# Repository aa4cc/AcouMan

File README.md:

# AcouMan - a platform for acoustic manipulation
[index](README.md)

# _!! IMPORTANT -- repository relocated !!_
Content in this repo is no longer updated.
Go to (https://gitlab.fel.cvut.cz/aa4cc/acouman/acouman-main) to get the latest version.
# _!! !!_

AcouMan is a platform for acoustic manipulation, that is for manipulating objects via shaping the surrounding acoustic pressure field. You can see the platform in the figure below and a detailed description will be (hopefully) published soon. If you want to see the platform in action, check our [video](https://youtu.be/BdDq_jRSNYA) showing some experiments with the platform.

This repository contains all files needed to reproduce the platform.

* [_MATLAB Optimization/_](MATLAB&#32;optimization/readme.md) folder contains Matlab scripts implementing a solver of the optimization problem where one looks for such phase shifts of the signals driving the transducer array that a given pressure point in space is generated
* [_FPGA generator/_](FPGA_generator/readme.md) folder contains a Quartus project for the 64 channel generator
* [_calibration/_](calibration/readme.md) folder contains all scripts for calibrating the camera
* [_manufacturing/_](manufacturing/readme.md) folder contains all drawings for a laser cutter, 3D models and PCB designs for manufacturing the platform
* [_simulink/_](simulink/readme.md) folder contains Simulink schemes for controlling the platform in various modes
* [_visualization/_](visualization/readme.md) folder contains Matlab scripts for visualization of the generated pressure field by the transducer array driven by square waves with specified phase-shifts
* [_webinterface/_](webinterface/readme.md) folder contains Python scripts for the web interface running on the Raspberry Pi

## Building the platform

If you want to build the platform, please refer to the guides on [mechanical assembly](docs/assembly.md) and [software](docs/software.md).

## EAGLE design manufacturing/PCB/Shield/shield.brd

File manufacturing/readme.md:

# Manufacturing
[index](../README.md) \> [manufacturing](readme.md)

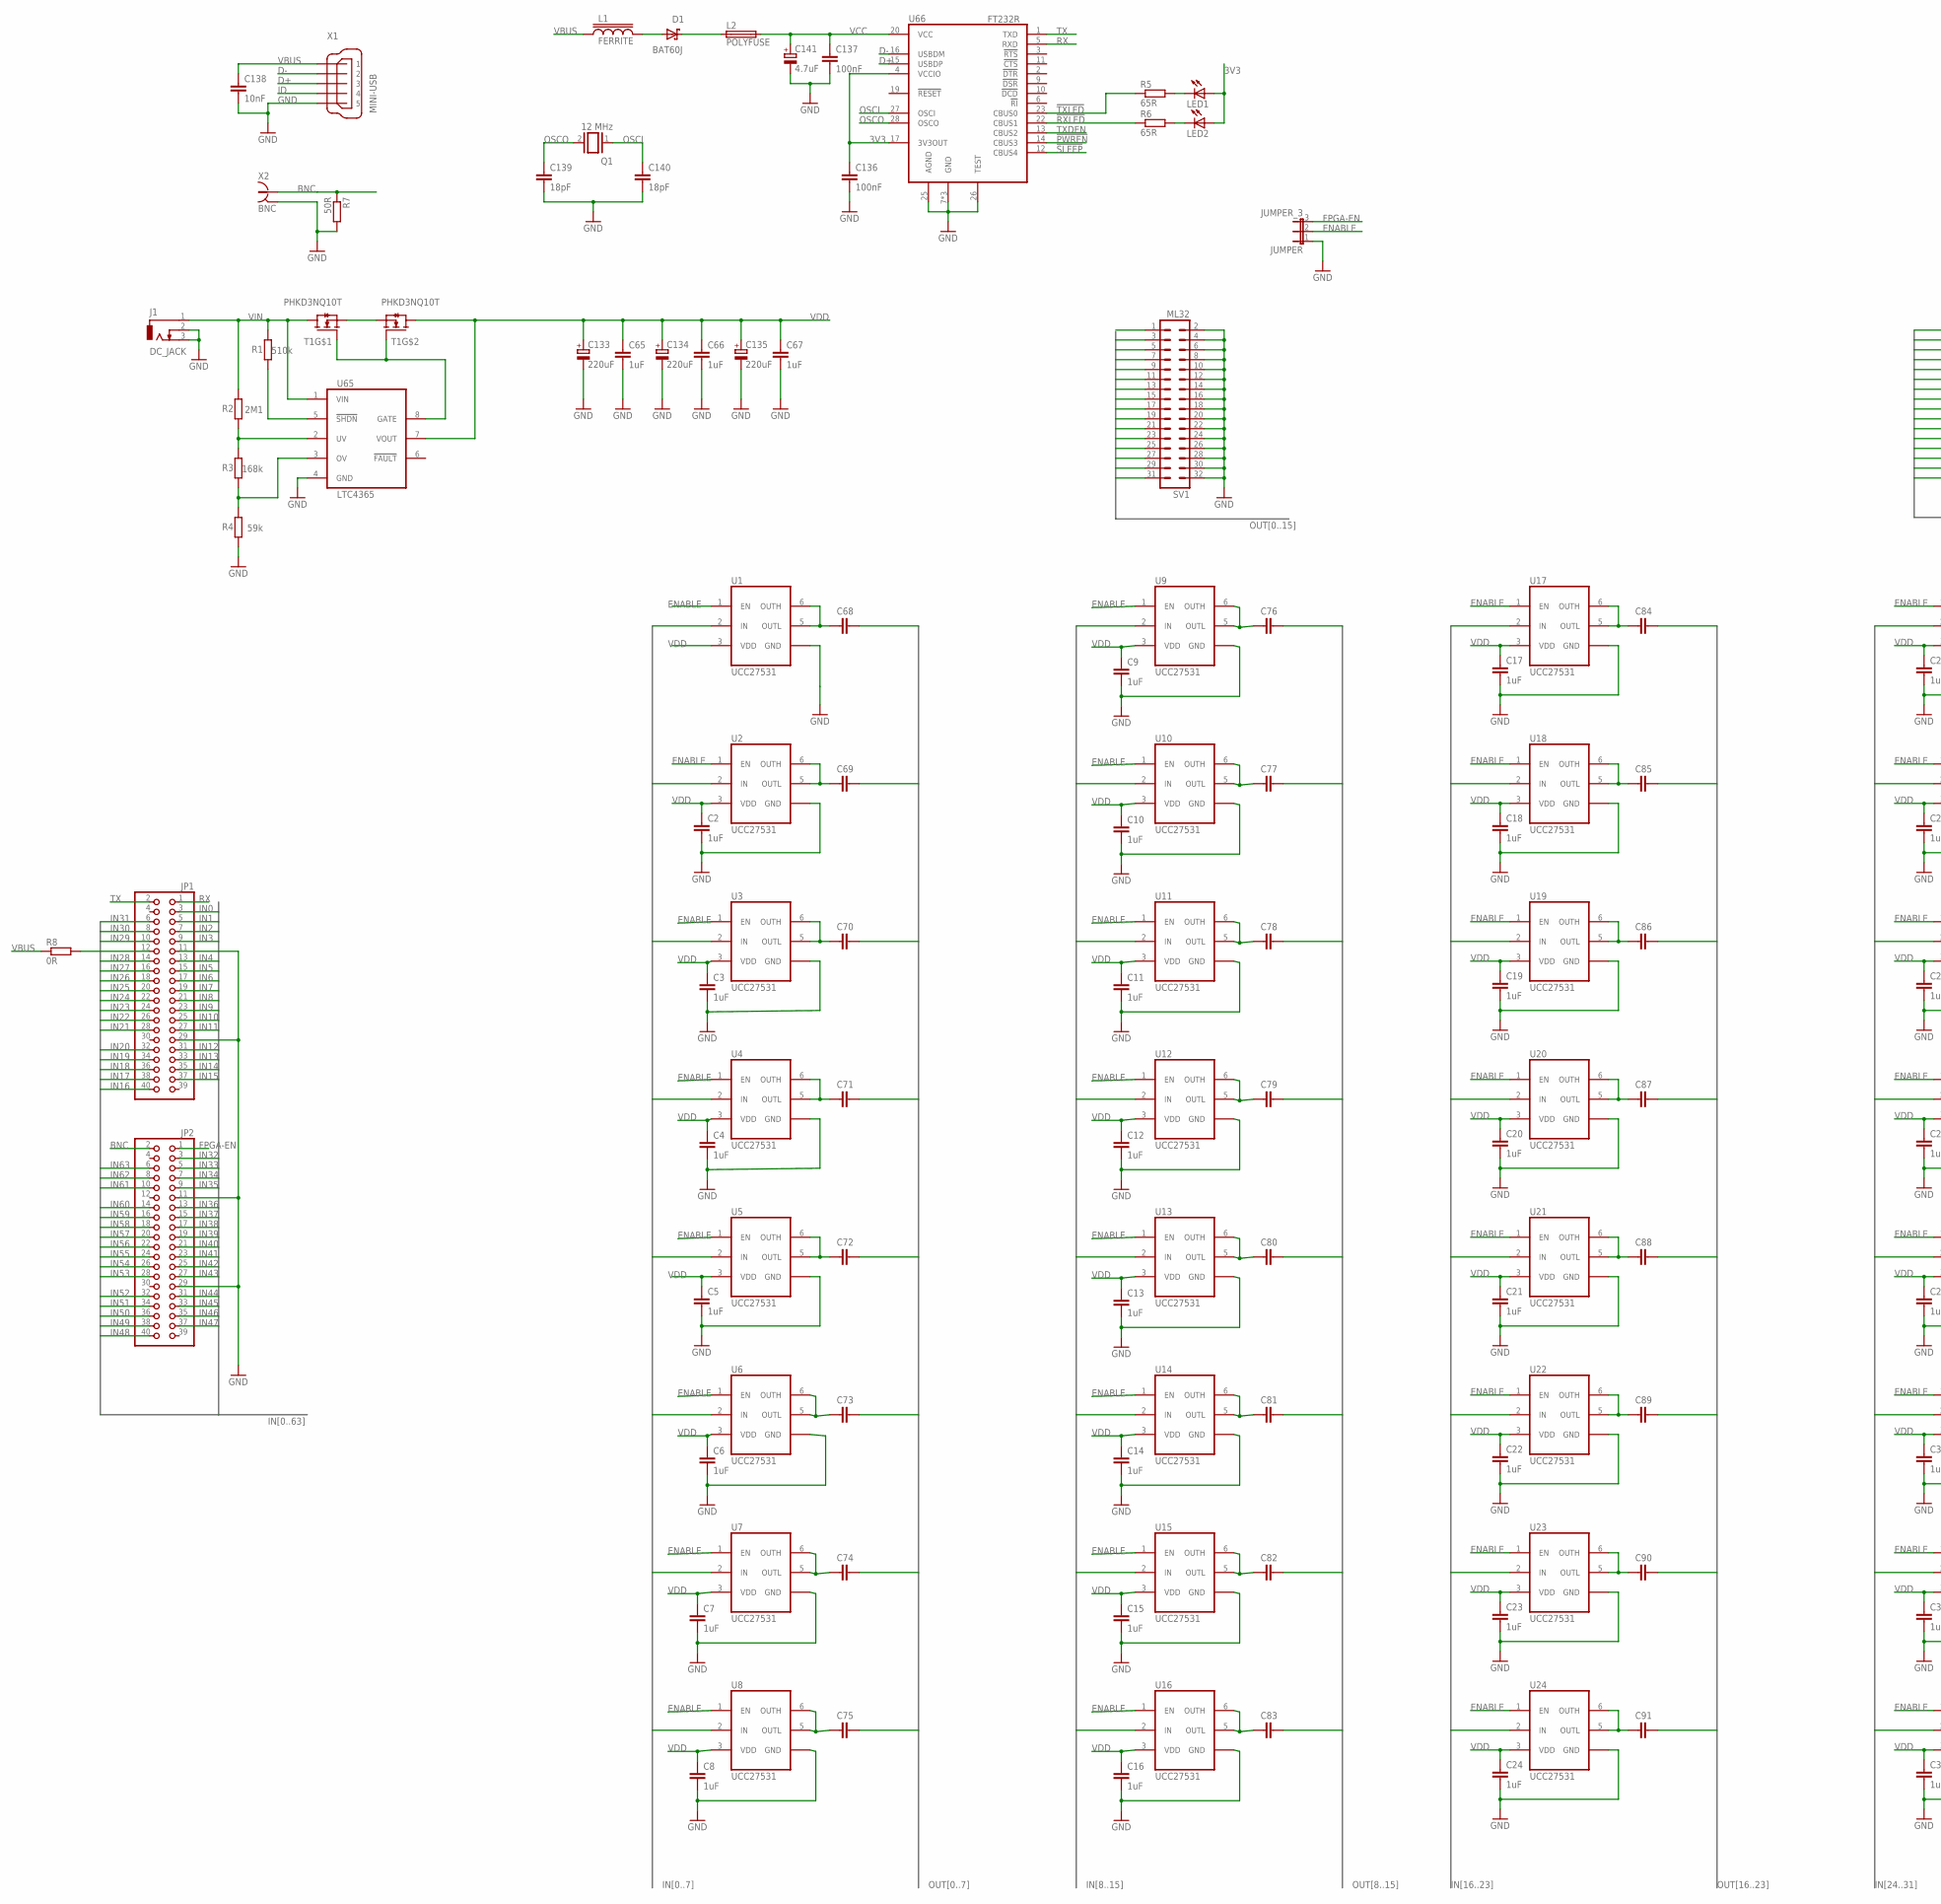
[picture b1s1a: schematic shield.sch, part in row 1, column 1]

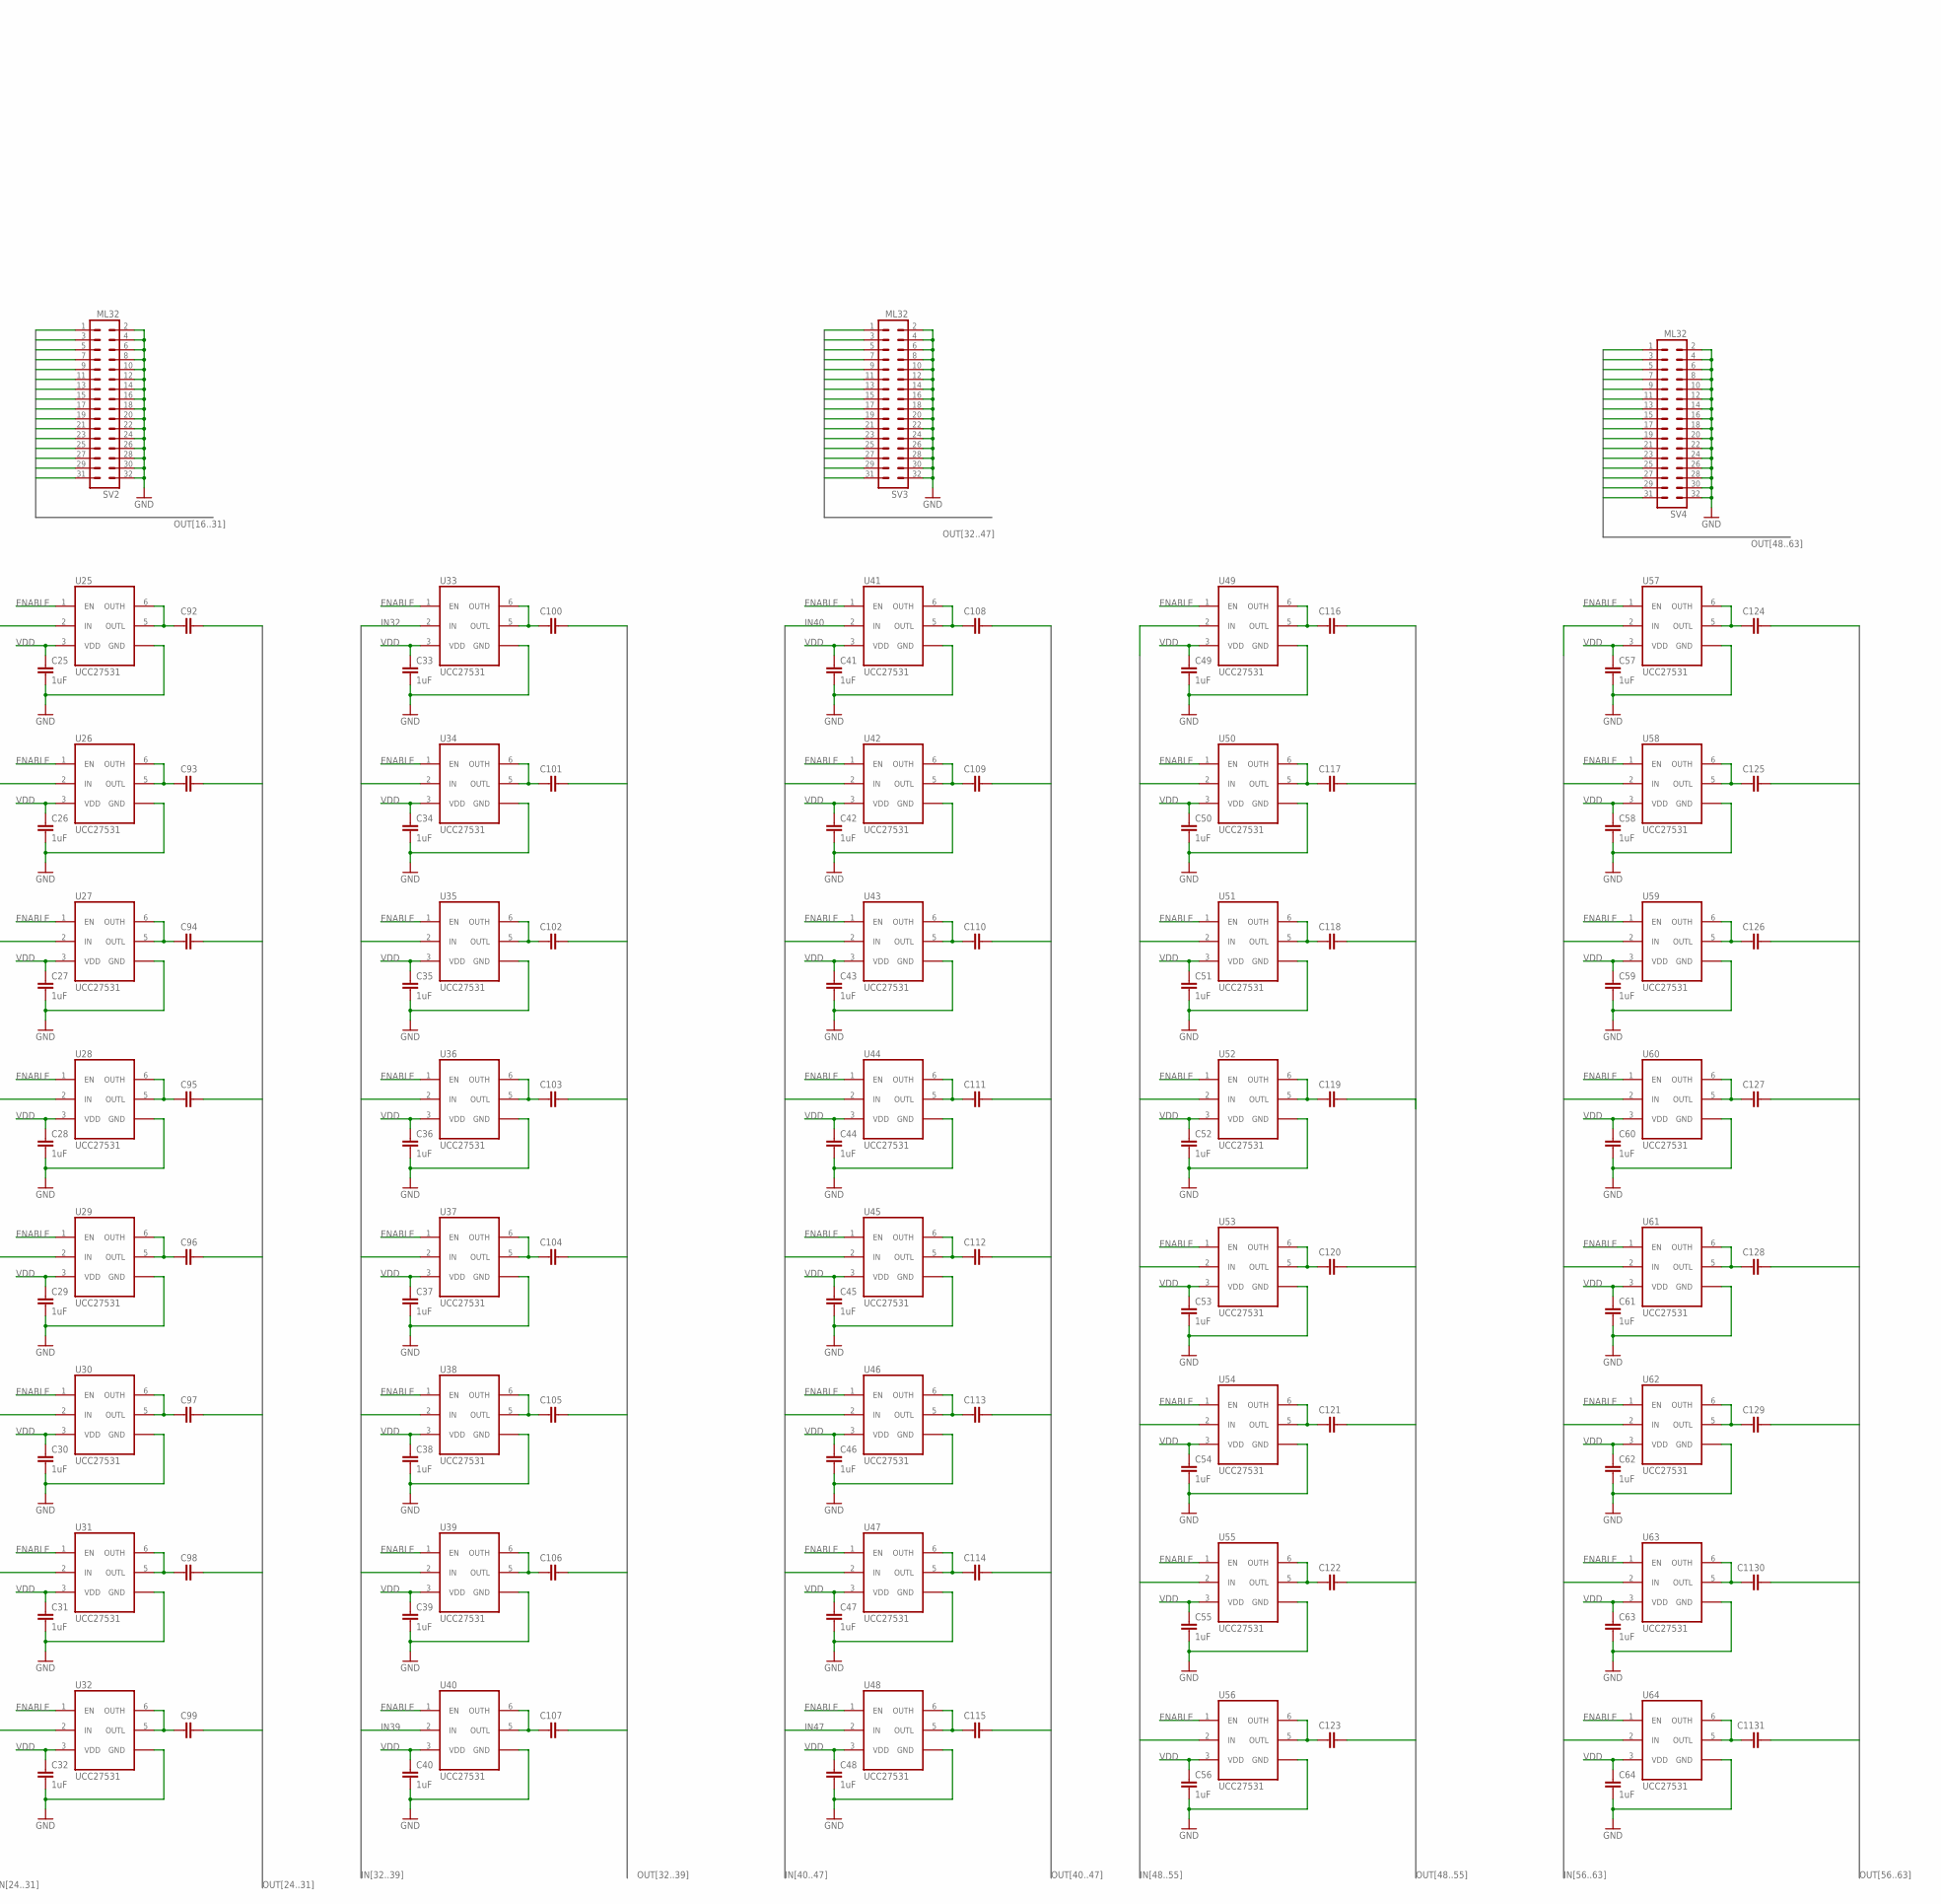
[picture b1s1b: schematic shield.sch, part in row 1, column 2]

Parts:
C2, C3, C4, C5, C6, C7, C8, C9, C10, C11, C12, C13, C14, C15, C16, C17, C18, C19, C20, C21, C22, C23, C24, C25, C26, C27, C28, C29, C30, C31, C32, C33, C34, C35, C36, C37, C38, C39, C40, C41, C42, C43, C44, C45, C46, C47, C48, C49, C50, C51, C52, C53, C54, C55, C56, C57, C58, C59, C60, C61, C62, C63, C64, C65, C66, C67: 1uF; C0805
C68, C69, C70, C71, C72, C73, C74, C75, C76, C77, C78, C79, C80, C81, C82, C83, C84, C85, C86, C87, C88, C89, C90, C91, C92, C93, C94, C95, C96, C97, C98, C99, C100, C101, C102, C103, C104, C105, C106, C107, C108, C109, C110, C111, C112, C113, C114, C115, C116, C117, C118, C119, C120, C121, C122, C123, C124, C125, C126, C127, C128, C129, C1130, C1131: C; C0805
C133, C134, C135: 220uF; E5-10,5
C136, C137: 100nF; C0805
C138: 10nF; C0805
C139, C140: 18pF; C0603
C141: 4.7uF; E2-5
D1: BAT60J; SOD323_ST
J1: DC_JACK; DCJ0202
JP1, JP2: PINHD-2X20; 2X20
JUMPER: JUMPER_3; JP2
L1: FERRITE; SML0805
L2: POLYFUSE; SML0805
LED1, LED2: LEDSML1206; SML1206
Q1: 12 MHz; QS
R1: 510k; R0805
R2: 2M1; R0805
R3: 168k; R0805
R4: 59k; R0805
R5, R6: 65R; R0805
R7: 50R; R0603
R8: 0R; R0805
SV1, SV2, SV3, SV4: ML32
T1: PHKD3NQ10T; SO8
U1, U2, U3, U4, U5, U6, U7, U8, U9, U10, U11, U12, U13, U14, U15, U16, U17, U18, U19, U20, U21, U22, U23, U24, U25, U26, U27, U28, U29, U30, U31, U32, U33, U34, U35, U36, U37, U38, U39, U40, U41, U42, U43, U44, U45, U46, U47, U48, U49, U50, U51, U52, U53, U54, U55, U56, U57, U58, U59, U60, U61, U62, U63, U64: UCC27531; DBV_R-PDSO-G6
U65: LTC4365; TSOT23-8
U66: FT232R; SSOP28
X1: MINI-USB; 32005-201
X2: BNC; BNC_CUSTOM

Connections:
3V3: C136.1, LED1.A, LED2.A, U66.4 (VCCIO), U66.17 (3V3OUT)
!PWREN!: U66.14 (CBUS3)
!RXLED!: R6.1, U66.22 (CBUS1)
!SLEEP!: U66.12 (CBUS4)
!TXLED!: R5.1, U66.23 (CBUS0)
BNC: JP2.2, R7.1, X2.1
D+: U66.15 (USBDP), X1.3
D-: U66.16 (USBDM), X1.2
ENABLE: JUMPER.2, U1.1 (EN), U2.1 (EN), U3.1 (EN), U4.1 (EN), U5.1 (EN), U6.1 (EN), U7.1 (EN), U8.1 (EN), U9.1 (EN), U10.1 (EN), U11.1 (EN), U12.1 (EN), U13.1 (EN), U14.1 (EN), U15.1 (EN), U16.1 (EN), U17.1 (EN), U18.1 (EN), U19.1 (EN), U20.1 (EN), U21.1 (EN), U22.1 (EN), U23.1 (EN), U24.1 (EN), U25.1 (EN), U26.1 (EN), U27.1 (EN), U28.1 (EN), U29.1 (EN), U30.1 (EN), U31.1 (EN), U32.1 (EN), U33.1 (EN), U34.1 (EN), U35.1 (EN), U36.1 (EN), U37.1 (EN), U38.1 (EN), U39.1 (EN), U40.1 (EN), U41.1 (EN), U42.1 (EN), U43.1 (EN), U44.1 (EN), U45.1 (EN), U46.1 (EN), U47.1 (EN), U48.1 (EN), U49.1 (EN), U50.1 (EN), U51.1 (EN), U52.1 (EN), U53.1 (EN), U54.1 (EN), U55.1 (EN), U56.1 (EN), U57.1 (EN), U58.1 (EN), U59.1 (EN), U60.1 (EN), U61.1 (EN), U62.1 (EN), U63.1 (EN), U64.1 (EN)
FPGA-EN: JP2.1, JUMPER.3
GND: C2.2, C3.2, C4.2, C5.2, C6.2, C7.2, C8.2, C9.2, C10.2, C11.2, C12.2, C13.2, C14.2, C15.2, C16.2, C17.2, C18.2, C19.2, C20.2, C21.2, C22.2, C23.2, C24.2, C25.2, C26.2, C27.2, C28.2, C29.2, C30.2, C31.2, C32.2, C33.2, C34.2, C35.2, C36.2, C37.2, C38.2, C39.2, C40.2, C41.2, C42.2, C43.2, C44.2, C45.2, C46.2, C47.2, C48.2, C49.2, C50.2, C51.2, C52.2, C53.2, C54.2, C55.2, C56.2, C57.2, C58.2, C59.2, C60.2, C61.2, C62.2, C63.2, C64.2, C65.2, C66.2, C67.2, C133.-, C134.-, C135.-, C136.2, C137.2, C138.2, C139.2, C140.2, C141.-, J1.2, J1.3, JP1.11, JP1.29, JP2.11, JP2.29, JUMPER.1, R4.1, R7.2, SV1.2, SV1.4, SV1.6, SV1.8, SV1.10, SV1.12, SV1.14, SV1.16, SV1.18, SV1.20, SV1.22, SV1.24, SV1.26, SV1.28, SV1.30, SV1.32, SV2.2, SV2.4, SV2.6, SV2.8, SV2.10, SV2.12, SV2.14, SV2.16, SV2.18, SV2.20, SV2.22, SV2.24, SV2.26, SV2.28, SV2.30, SV2.32, SV3.2, SV3.4, SV3.6, SV3.8, SV3.10, SV3.12, SV3.14, SV3.16, SV3.18, SV3.20, SV3.22, SV3.24, SV3.26, SV3.28, SV3.30, SV3.32, SV4.2, SV4.4, SV4.6, SV4.8, SV4.10, SV4.12, SV4.14, SV4.16, SV4.18, SV4.20, SV4.22, SV4.24, SV4.26, SV4.28, SV4.30, SV4.32, U1.4 (GND), U2.4 (GND), U3.4 (GND), U4.4 (GND), U5.4 (GND), U6.4 (GND)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
ID: X1.4
IN0: JP1.3, U1.2 (IN)
IN1: JP1.5, U2.2 (IN)
IN2: JP1.7, U3.2 (IN)
IN3: JP1.9, U4.2 (IN)
IN4: JP1.13, U5.2 (IN)
IN5: JP1.15, U6.2 (IN)
IN6: JP1.17, U7.2 (IN)
IN7: JP1.19, U8.2 (IN)
IN8: JP1.21, U9.2 (IN)
IN9: JP1.23, U10.2 (IN)
IN10: JP1.25, U11.2 (IN)
IN11: JP1.27, U12.2 (IN)
IN12: JP1.31, U13.2 (IN)
IN13: JP1.33, U14.2 (IN)
IN14: JP1.35, U15.2 (IN)
IN15: JP1.37, U16.2 (IN)
IN16: JP1.40, U17.2 (IN)
IN17: JP1.38, U18.2 (IN)
IN18: JP1.36, U19.2 (IN)
IN19: JP1.34, U20.2 (IN)
IN20: JP1.32, U21.2 (IN)
IN21: JP1.28, U22.2 (IN)
IN22: JP1.26, U23.2 (IN)
IN23: JP1.24, U24.2 (IN)
IN24: JP1.22, U25.2 (IN)
IN25: JP1.20, U26.2 (IN)
IN26: JP1.18, U27.2 (IN)
IN27: JP1.16, U28.2 (IN)
IN28: JP1.14, U29.2 (IN)
IN29: JP1.10, U30.2 (IN)
IN30: JP1.8, U31.2 (IN)
IN31: JP1.6, U32.2 (IN)
IN32: JP2.3, U33.2 (IN)
IN33: JP2.5, U34.2 (IN)
IN34: JP2.7, U35.2 (IN)
IN35: JP2.9, U36.2 (IN)
IN36: JP2.13, U37.2 (IN)
IN37: JP2.15, U38.2 (IN)
IN38: JP2.17, U39.2 (IN)
IN39: JP2.19, U40.2 (IN)
IN40: JP2.21, U41.2 (IN)
IN41: JP2.23, U42.2 (IN)
IN42: JP2.25, U43.2 (IN)
IN43: JP2.27, U44.2 (IN)
IN44: JP2.31, U45.2 (IN)
IN45: JP2.33, U46.2 (IN)
IN46: JP2.35, U47.2 (IN)
IN47: JP2.37, U48.2 (IN)
IN48: JP2.40, U49.2 (IN)
IN49: JP2.38, U50.2 (IN)
IN50: JP2.36, U51.2 (IN)
IN51: JP2.34, U52.2 (IN)
IN52: JP2.32, U53.2 (IN)
IN53: JP2.28, U54.2 (IN)
IN54: JP2.26, U55.2 (IN)
IN55: JP2.24, U56.2 (IN)
IN56: JP2.22, U57.2 (IN)
IN57: JP2.20, U58.2 (IN)
IN58: JP2.18, U59.2 (IN)
IN59: JP2.16, U60.2 (IN)
IN60: JP2.14, U61.2 (IN)
IN61: JP2.10, U62.2 (IN)
IN62: JP2.8, U63.2 (IN)
IN63: JP2.6, U64.2 (IN)
unnamed: JP1.12, R8.2
unnamed: D1.C, L2.A (1)
unnamed: D1.A, L1.C (2)
unnamed: R1.1, U65.5 (!SHDN!)
unnamed: R2.1, R3.2, U65.2 (UV)
unnamed: R3.1, R4.2, U65.3 (OV)
unnamed: T1.1 (S), T1.3 (S)
unnamed: T1.2 (G), T1.4 (G), U65.8 (GATE)
unnamed: LED1.C, R5.2
unnamed: LED2.C, R6.2
unnamed: C100.1, U33.5 (OUTL), U33.6 (OUTH)
unnamed: C101.1, U34.5 (OUTL), U34.6 (OUTH)
unnamed: C102.1, U35.5 (OUTL), U35.6 (OUTH)
unnamed: C103.1, U36.5 (OUTL), U36.6 (OUTH)
unnamed: C104.1, U37.5 (OUTL), U37.6 (OUTH)
unnamed: C105.1, U38.5 (OUTL), U38.6 (OUTH)
unnamed: C106.1, U39.5 (OUTL), U39.6 (OUTH)
unnamed: C107.1, U40.5 (OUTL), U40.6 (OUTH)
unnamed: C108.1, U41.5 (OUTL), U41.6 (OUTH)
unnamed: C109.1, U42.5 (OUTL), U42.6 (OUTH)
unnamed: C110.1, U43.5 (OUTL), U43.6 (OUTH)
unnamed: C111.1, U44.5 (OUTL), U44.6 (OUTH)
unnamed: C112.1, U45.5 (OUTL), U45.6 (OUTH)
unnamed: C113.1, U46.5 (OUTL), U46.6 (OUTH)
unnamed: C114.1, U47.5 (OUTL), U47.6 (OUTH)
unnamed: C115.1, U48.5 (OUTL), U48.6 (OUTH)
unnamed: C84.1, U17.5 (OUTL), U17.6 (OUTH)
unnamed: C85.1, U18.5 (OUTL), U18.6 (OUTH)
unnamed: C86.1, U19.5 (OUTL), U19.6 (OUTH)
unnamed: C87.1, U20.5 (OUTL), U20.6 (OUTH)
unnamed: C88.1, U21.5 (OUTL), U21.6 (OUTH)
unnamed: C89.1, U22.5 (OUTL), U22.6 (OUTH)
unnamed: C90.1, U23.5 (OUTL), U23.6 (OUTH)
unnamed: C91.1, U24.5 (OUTL), U24.6 (OUTH)
unnamed: C92.1, U25.5 (OUTL), U25.6 (OUTH)
unnamed: C93.1, U26.5 (OUTL), U26.6 (OUTH)
unnamed: C94.1, U27.5 (OUTL), U27.6 (OUTH)
unnamed: C95.1, U28.5 (OUTL), U28.6 (OUTH)
unnamed: C96.1, U29.5 (OUTL), U29.6 (OUTH)
unnamed: C97.1, U30.5 (OUTL), U30.6 (OUTH)
unnamed: C98.1, U31.5 (OUTL), U31.6 (OUTH)
unnamed: C99.1, U32.5 (OUTL), U32.6 (OUTH)
unnamed: C68.1, U1.5 (OUTL), U1.6 (OUTH)
unnamed: C69.1, U2.5 (OUTL), U2.6 (OUTH)
unnamed: C70.1, U3.5 (OUTL), U3.6 (OUTH)
unnamed: C71.1, U4.5 (OUTL), U4.6 (OUTH)
unnamed: C72.1, U5.5 (OUTL), U5.6 (OUTH)
unnamed: C73.1, U6.5 (OUTL), U6.6 (OUTH)
unnamed: C74.1, U7.5 (OUTL), U7.6 (OUTH)
unnamed: C75.1, U8.5 (OUTL), U8.6 (OUTH)
unnamed: C76.1, U9.5 (OUTL), U9.6 (OUTH)
unnamed: C77.1, U10.5 (OUTL), U10.6 (OUTH)
unnamed: C78.1, U11.5 (OUTL), U11.6 (OUTH)
unnamed: C79.1, U12.5 (OUTL), U12.6 (OUTH)
unnamed: C80.1, U13.5 (OUTL), U13.6 (OUTH)
unnamed: C81.1, U14.5 (OUTL), U14.6 (OUTH)
unnamed: C82.1, U15.5 (OUTL), U15.6 (OUTH)
unnamed: C83.1, U16.5 (OUTL), U16.6 (OUTH)
unnamed: C116.1, U49.5 (OUTL), U49.6 (OUTH)
unnamed: C117.1, U50.5 (OUTL), U50.6 (OUTH)
unnamed: C118.1, U51.5 (OUTL), U51.6 (OUTH)
unnamed: C119.1, U52.5 (OUTL), U52.6 (OUTH)
unnamed: C120.1, U53.5 (OUTL), U53.6 (OUTH)
unnamed: C121.1, U54.5 (OUTL), U54.6 (OUTH)
unnamed: C122.1, U55.5 (OUTL), U55.6 (OUTH)
unnamed: C123.1, U56.5 (OUTL), U56.6 (OUTH)
unnamed: C124.1, U57.5 (OUTL), U57.6 (OUTH)
unnamed: C125.1, U58.5 (OUTL), U58.6 (OUTH)
unnamed: C126.1, U59.5 (OUTL), U59.6 (OUTH)
unnamed: C127.1, U60.5 (OUTL), U60.6 (OUTH)
unnamed: C128.1, U61.5 (OUTL), U61.6 (OUTH)
unnamed: C129.1, U62.5 (OUTL), U62.6 (OUTH)
unnamed: C1130.1, U63.5 (OUTL), U63.6 (OUTH)
unnamed: C1131.1, U64.5 (OUTL), U64.6 (OUTH)
OSCI: C140.1, Q1.1, U66.27 (OSCI)
OSCO: C139.1, Q1.2, U66.28 (OSCO)
OUT0: C68.2, SV1.1
OUT1: C69.2, SV1.3
OUT2: C70.2, SV1.5
OUT3: C71.2, SV1.7
OUT4: C72.2, SV1.9
OUT5: C73.2, SV1.11
OUT6: C74.2, SV1.13
OUT7: C75.2, SV1.15
OUT8: C76.2, SV1.17
OUT9: C77.2, SV1.19
OUT10: C78.2, SV1.21
OUT11: C79.2, SV1.23
OUT12: C80.2, SV1.25
OUT13: C81.2, SV1.27
OUT14: C82.2, SV1.29
OUT15: C83.2, SV1.31
OUT16: C84.2, SV2.1
OUT17: C85.2, SV2.3
OUT18: C86.2, SV2.5
OUT19: C87.2, SV2.7
OUT20: C88.2, SV2.9
OUT21: C89.2, SV2.11
OUT22: C90.2, SV2.13
OUT23: C91.2, SV2.15
OUT24: C92.2, SV2.17
OUT25: C93.2, SV2.19
OUT26: C94.2, SV2.21
OUT27: C95.2, SV2.23
OUT28: C96.2, SV2.25
OUT29: C97.2, SV2.27
OUT30: C98.2, SV2.29
OUT31: C99.2, SV2.31
OUT32: C100.2, SV3.1
OUT33: C101.2, SV3.3
OUT34: C102.2, SV3.5
OUT35: C103.2, SV3.7
OUT36: C104.2, SV3.9
OUT37: C105.2, SV3.11
OUT38: C106.2, SV3.13
OUT39: C107.2, SV3.15
OUT40: C108.2, SV3.17
OUT41: C109.2, SV3.19
OUT42: C110.2, SV3.21
OUT43: C111.2, SV3.23
OUT44: C112.2, SV3.25
OUT45: C113.2, SV3.27
OUT46: C114.2, SV3.29
OUT47: C115.2, SV3.31
OUT48: C116.2, SV4.1
OUT49: C117.2, SV4.3
OUT50: C118.2, SV4.5
OUT51: C119.2, SV4.7
OUT52: C120.2, SV4.9
OUT53: C121.2, SV4.11
OUT54: C122.2, SV4.13
OUT55: C123.2, SV4.15
OUT56: C124.2, SV4.17
OUT57: C125.2, SV4.19
OUT58: C126.2, SV4.21
OUT59: C127.2, SV4.23
OUT60: C128.2, SV4.25
OUT61: C129.2, SV4.27
OUT62: C1130.2, SV4.29
OUT63: C1131.2, SV4.31
RX: JP1.1, U66.5 (RXD)
TX: JP1.2, U66.1 (TXD)
TXDEN: U66.13 (CBUS2)
VBUS: C138.1, L1.A (1), R8.1, X1.1
VCC: C137.1, C141.+, L2.C (2), U66.20 (VCC)
VDD: C2.1, C3.1, C4.1, C5.1, C6.1, C7.1, C8.1, C9.1, C10.1, C11.1, C12.1, C13.1, C14.1, C15.1, C16.1, C17.1, C18.1, C19.1, C20.1, C21.1, C22.1, C23.1, C24.1, C25.1, C26.1, C27.1, C28.1, C29.1, C30.1, C31.1, C32.1, C33.1, C34.1, C35.1, C36.1, C37.1, C38.1, C39.1, C40.1, C41.1, C42.1, C43.1, C44.1, C45.1, C46.1, C47.1, C48.1, C49.1, C50.1, C51.1, C52.1, C53.1, C54.1, C55.1, C56.1, C57.1, C58.1, C59.1, C60.1, C61.1, C62.1, C63.1, C64.1, C65.1, C66.1, C67.1, C133.+, C134.+, C135.+, T1.5 (D), T1.6 (D), U1.3 (VDD), U2.3 (VDD), U3.3 (VDD), U4.3 (VDD), U5.3 (VDD), U6.3 (VDD), U7.3 (VDD), U8.3 (VDD), U9.3 (VDD), U10.3 (VDD), U11.3 (VDD), U12.3 (VDD), U13.3 (VDD), U14.3 (VDD), U15.3 (VDD), U16.3 (VDD), U17.3 (VDD), U18.3 (VDD), U19.3 (VDD), U20.3 (VDD), U21.3 (VDD), U22.3 (VDD), U23.3 (VDD), U24.3 (VDD), U25.3 (VDD), U26.3 (VDD), U27.3 (VDD), U28.3 (VDD), U29.3 (VDD), U30.3 (VDD), U31.3 (VDD), U32.3 (VDD), U33.3 (VDD), U34.3 (VDD), U35.3 (VDD), U36.3 (VDD), U37.3 (VDD), U38.3 (VDD), U39.3 (VDD), U40.3 (VDD), U41.3 (VDD), U42.3 (VDD), U43.3 (VDD), U44.3 (VDD), U45.3 (VDD), U46.3 (VDD), U47.3 (VDD), U48.3 (VDD), U49.3 (VDD), U50.3 (VDD), U51.3 (VDD), U52.3 (VDD), U53.3 (VDD), U54.3 (VDD), U55.3 (VDD), U56.3 (VDD), U57.3 (VDD), U58.3 (VDD), U59.3 (VDD), U60.3 (VDD), U61.3 (VDD), U62.3 (VDD), U63.3 (VDD), U64.3 (VDD), U65.7 (VOUT)
VIN: J1.1, R1.2, R2.2, T1.7 (D), T1.8 (D), U65.1 (VIN)

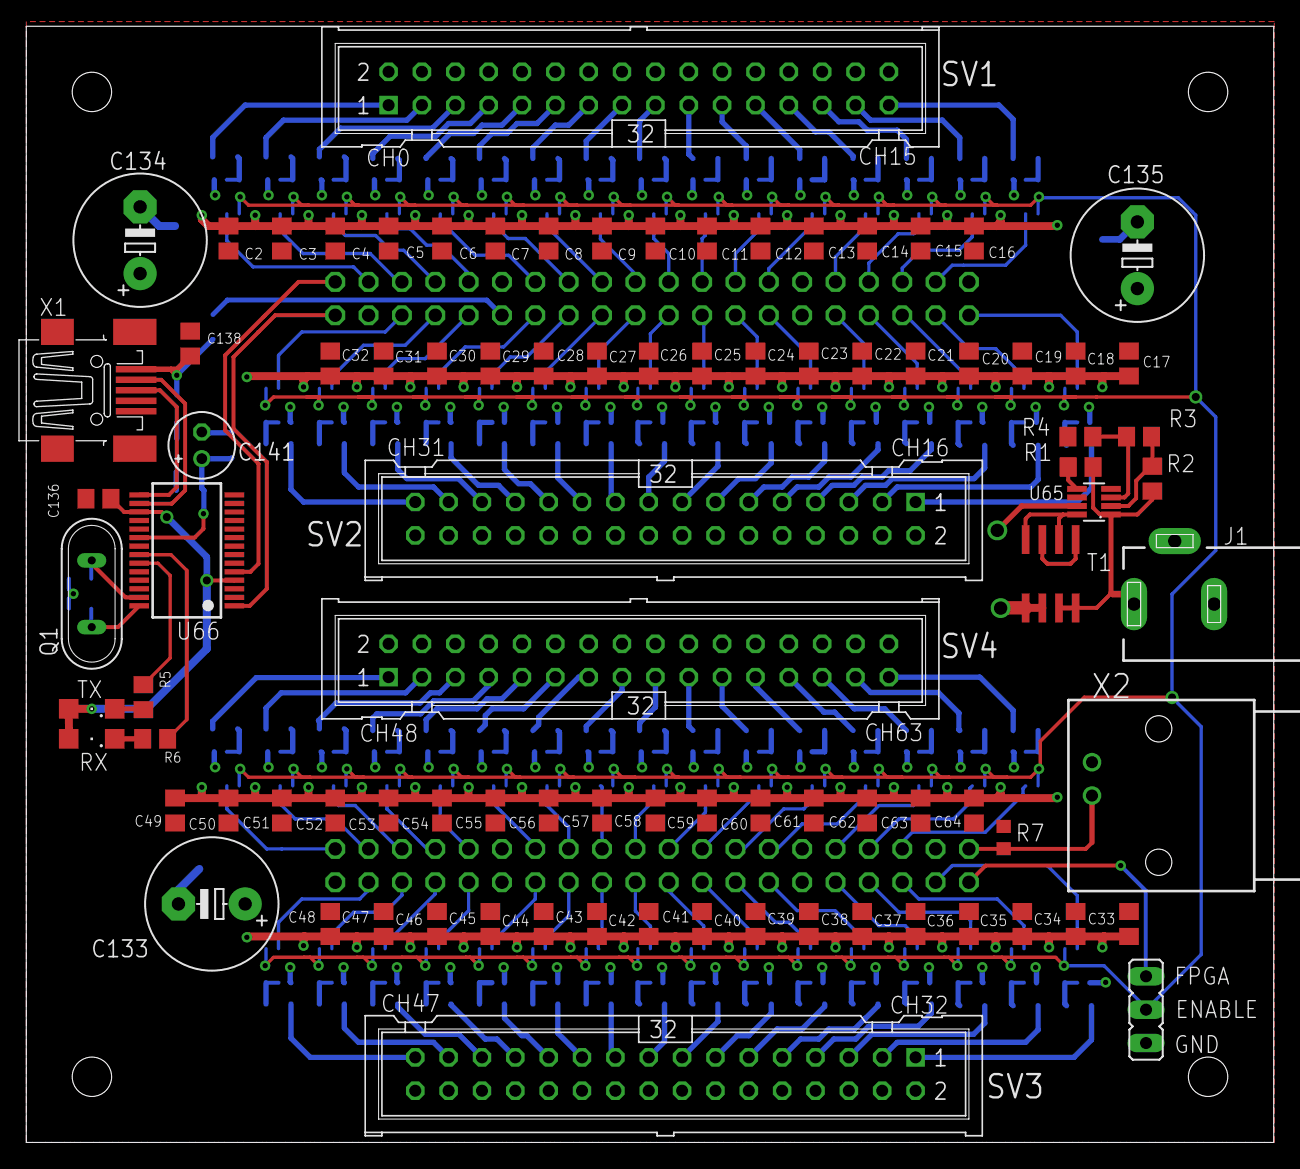
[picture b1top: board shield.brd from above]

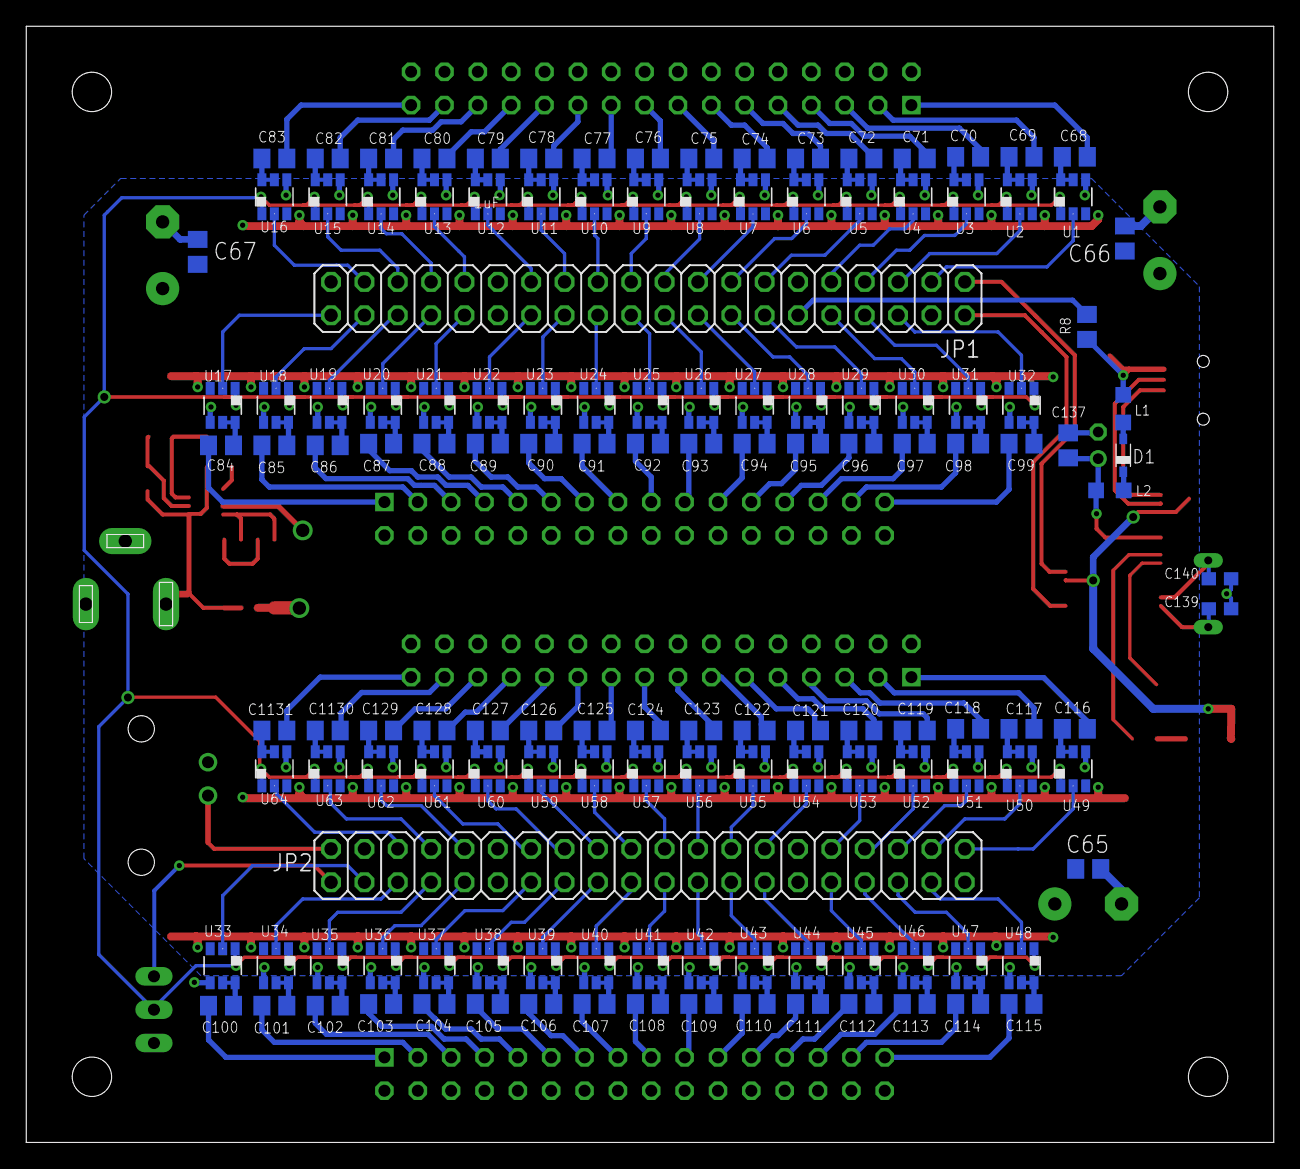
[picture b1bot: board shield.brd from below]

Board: 2 copper layers, 95.0 x 85.0 mm, 230 parts (140 on the bottom side), 219 nets.

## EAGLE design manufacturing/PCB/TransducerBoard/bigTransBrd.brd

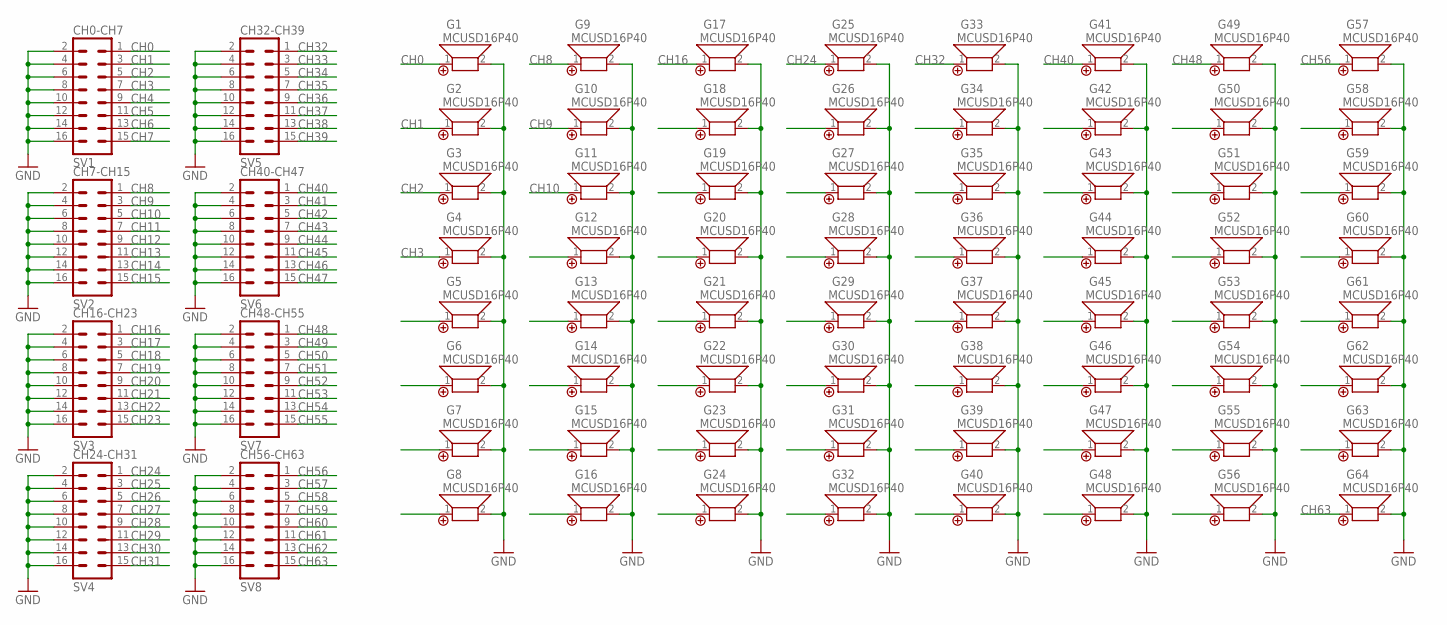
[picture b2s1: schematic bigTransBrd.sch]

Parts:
G1, G2, G3, G4, G5, G6, G7, G8, G9, G10, G11, G12, G13, G14, G15, G16, G17, G18, G19, G20, G21, G22, G23, G24, G25, G26, G27, G28, G29, G30, G31, G32, G33, G34, G35, G36, G37, G38, G39, G40, G41, G42, G43, G44, G45, G46, G47, G48, G49, G50, G51, G52, G53, G54, G55, G56, G57, G58, G59, G60, G61, G62, G63, G64: MCUSD16P40; D16P40
SV1: CH0-CH7; ML16
SV2: CH7-CH15; ML16
SV3: CH16-CH23; ML16
SV4: CH24-CH31; ML16
SV5: CH32-CH39; ML16
SV6: CH40-CH47; ML16
SV7: CH48-CH55; ML16
SV8: CH56-CH63; ML16

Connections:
CH0: G1.1, SV1.1
CH1: G2.1, SV1.3
CH2: G3.1, SV1.5
CH3: G4.1, SV1.7
CH4: G5.1, SV1.9
CH5: G6.1, SV1.11
CH6: G7.1, SV1.13
CH7: G8.1, SV1.15
CH8: G9.1, SV2.1
CH9: G10.1, SV2.3
CH10: G11.1, SV2.5
CH11: G12.1, SV2.7
CH12: G13.1, SV2.9
CH13: G14.1, SV2.11
CH14: G15.1, SV2.13
CH15: G16.1, SV2.15
CH16: G17.1, SV3.1
CH17: G18.1, SV3.3
CH18: G19.1, SV3.5
CH19: G20.1, SV3.7
CH20: G21.1, SV3.9
CH21: G22.1, SV3.11
CH22: G23.1, SV3.13
CH23: G24.1, SV3.15
CH24: G25.1, SV4.1
CH25: G26.1, SV4.3
CH26: G27.1, SV4.5
CH27: G28.1, SV4.7
CH28: G29.1, SV4.9
CH29: G30.1, SV4.11
CH30: G31.1, SV4.13
CH31: G32.1, SV4.15
CH32: G33.1, SV5.1
CH33: G34.1, SV5.3
CH34: G35.1, SV5.5
CH35: G36.1, SV5.7
CH36: G37.1, SV5.9
CH37: G38.1, SV5.11
CH38: G39.1, SV5.13
CH39: G40.1, SV5.15
CH40: G41.1, SV6.1
CH41: G42.1, SV6.3
CH42: G43.1, SV6.5
CH43: G44.1, SV6.7
CH44: G45.1, SV6.9
CH45: G46.1, SV6.11
CH46: G47.1, SV6.13
CH47: G48.1, SV6.15
CH48: G49.1, SV7.1
CH49: G50.1, SV7.3
CH50: G51.1, SV7.5
CH51: G52.1, SV7.7
CH52: G53.1, SV7.9
CH53: G54.1, SV7.11
CH54: G55.1, SV7.13
CH55: G56.1, SV7.15
CH56: G57.1, SV8.1
CH57: G58.1, SV8.3
CH58: G59.1, SV8.5
CH59: G60.1, SV8.7
CH60: G61.1, SV8.9
CH61: G62.1, SV8.11
CH62: G63.1, SV8.13
CH63: G64.1, SV8.15
GND: G1.2, G2.2, G3.2, G4.2, G5.2, G6.2, G7.2, G8.2, G9.2, G10.2, G11.2, G12.2, G13.2, G14.2, G15.2, G16.2, G17.2, G18.2, G19.2, G20.2, G21.2, G22.2, G23.2, G24.2, G25.2, G26.2, G27.2, G28.2, G29.2, G30.2, G31.2, G32.2, G33.2, G34.2, G35.2, G36.2, G37.2, G38.2, G39.2, G40.2, G41.2, G42.2, G43.2, G44.2, G45.2, G46.2, G47.2, G48.2, G49.2, G50.2, G51.2, G52.2, G53.2, G54.2, G55.2, G56.2, G57.2, G58.2, G59.2, G60.2, G61.2, G62.2, G63.2, G64.2, SV1.2, SV1.4, SV1.6, SV1.8, SV1.10, SV1.12, SV1.14, SV1.16, SV2.2, SV2.4, SV2.6, SV2.8, SV2.10, SV2.12, SV2.14, SV2.16, SV3.2, SV3.4, SV3.6, SV3.8, SV3.10, SV3.12, SV3.14, SV3.16, SV4.2, SV4.4, SV4.6, SV4.8, SV4.10, SV4.12, SV4.14, SV4.16, SV5.2, SV5.4, SV5.6, SV5.8, SV5.10, SV5.12, SV5.14, SV5.16, SV6.2, SV6.4, SV6.6, SV6.8, SV6.10, SV6.12, SV6.14, SV6.16, SV7.2, SV7.4, SV7.6, SV7.8, SV7.10, SV7.12, SV7.14, SV7.16, SV8.2, SV8.4, SV8.6, SV8.8, SV8.10, SV8.12, SV8.14, SV8.16

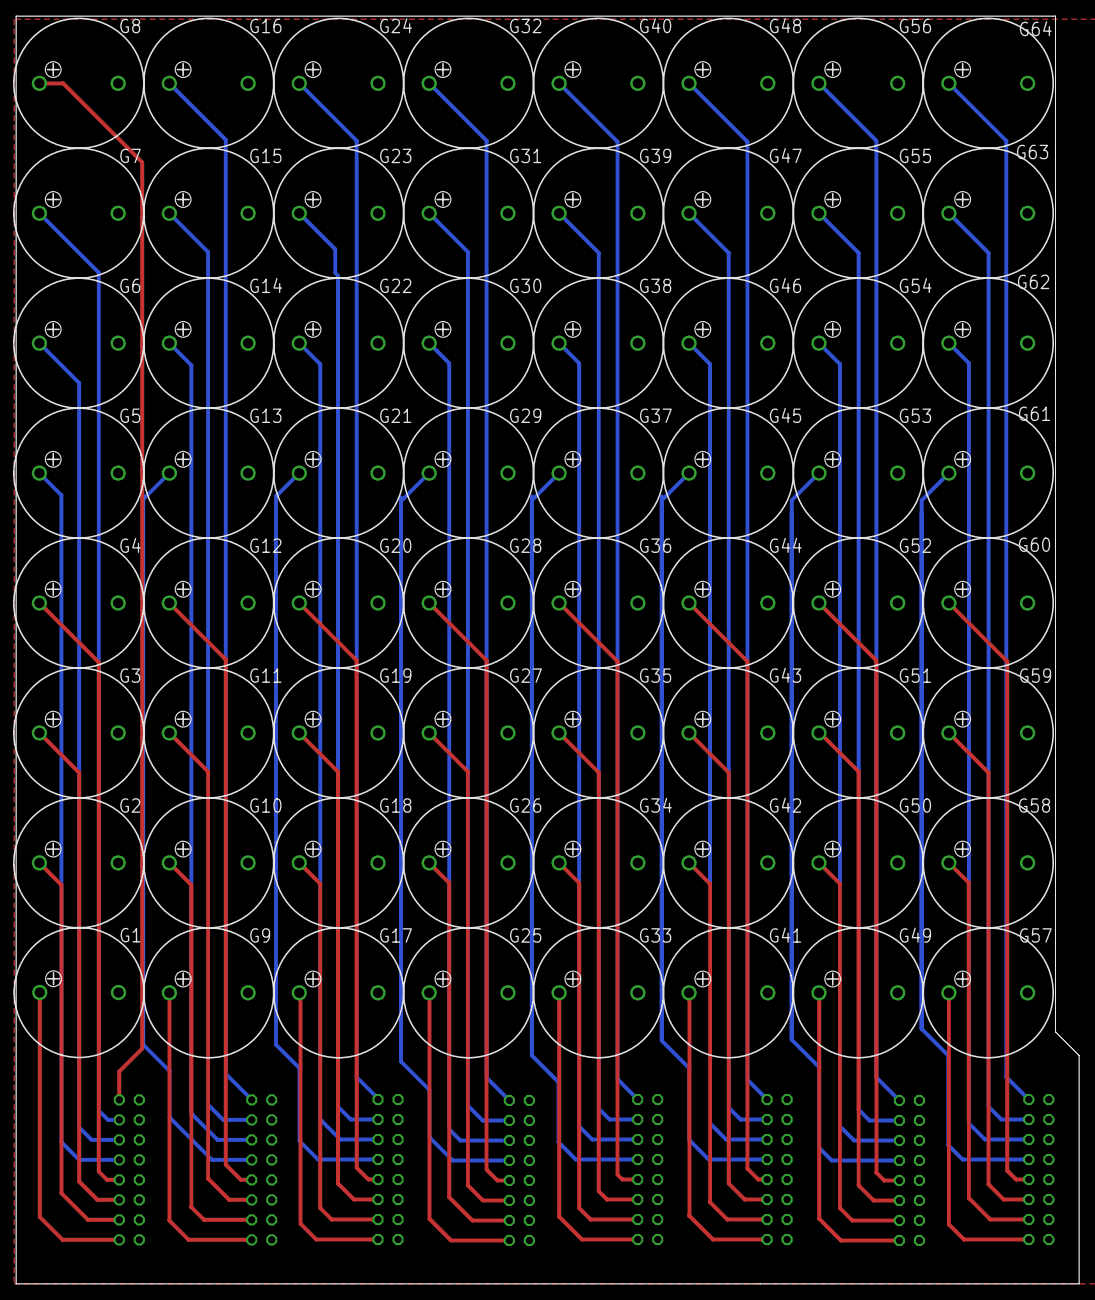
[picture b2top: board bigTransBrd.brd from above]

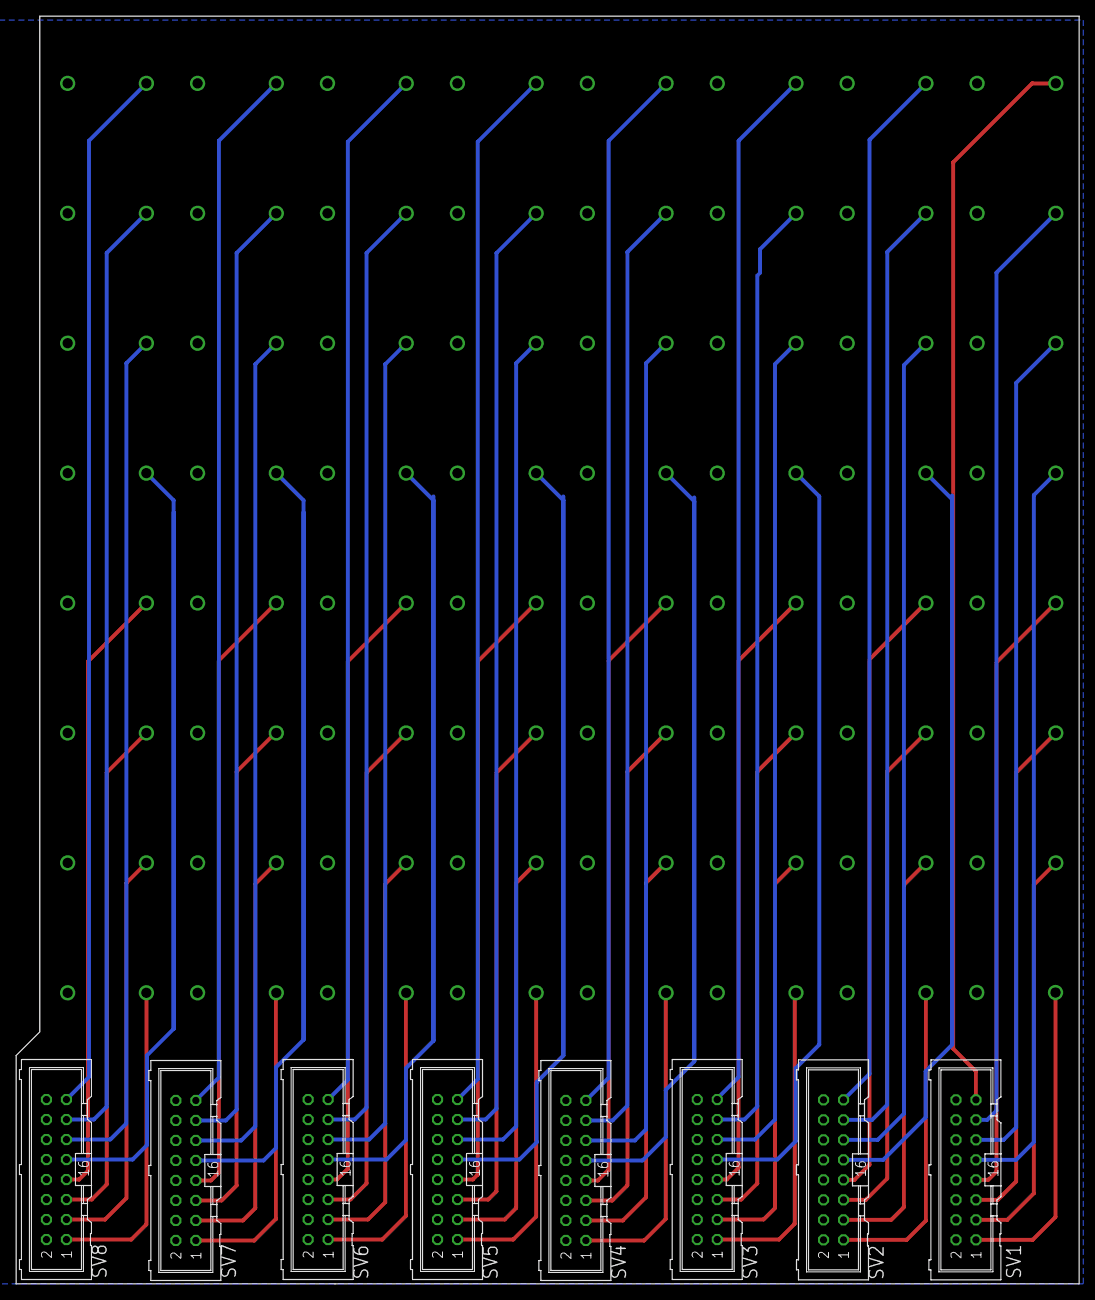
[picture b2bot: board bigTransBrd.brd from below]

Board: 2 copper layers, 135.0 x 161.0 mm, 72 parts (8 on the bottom side), 65 nets.
